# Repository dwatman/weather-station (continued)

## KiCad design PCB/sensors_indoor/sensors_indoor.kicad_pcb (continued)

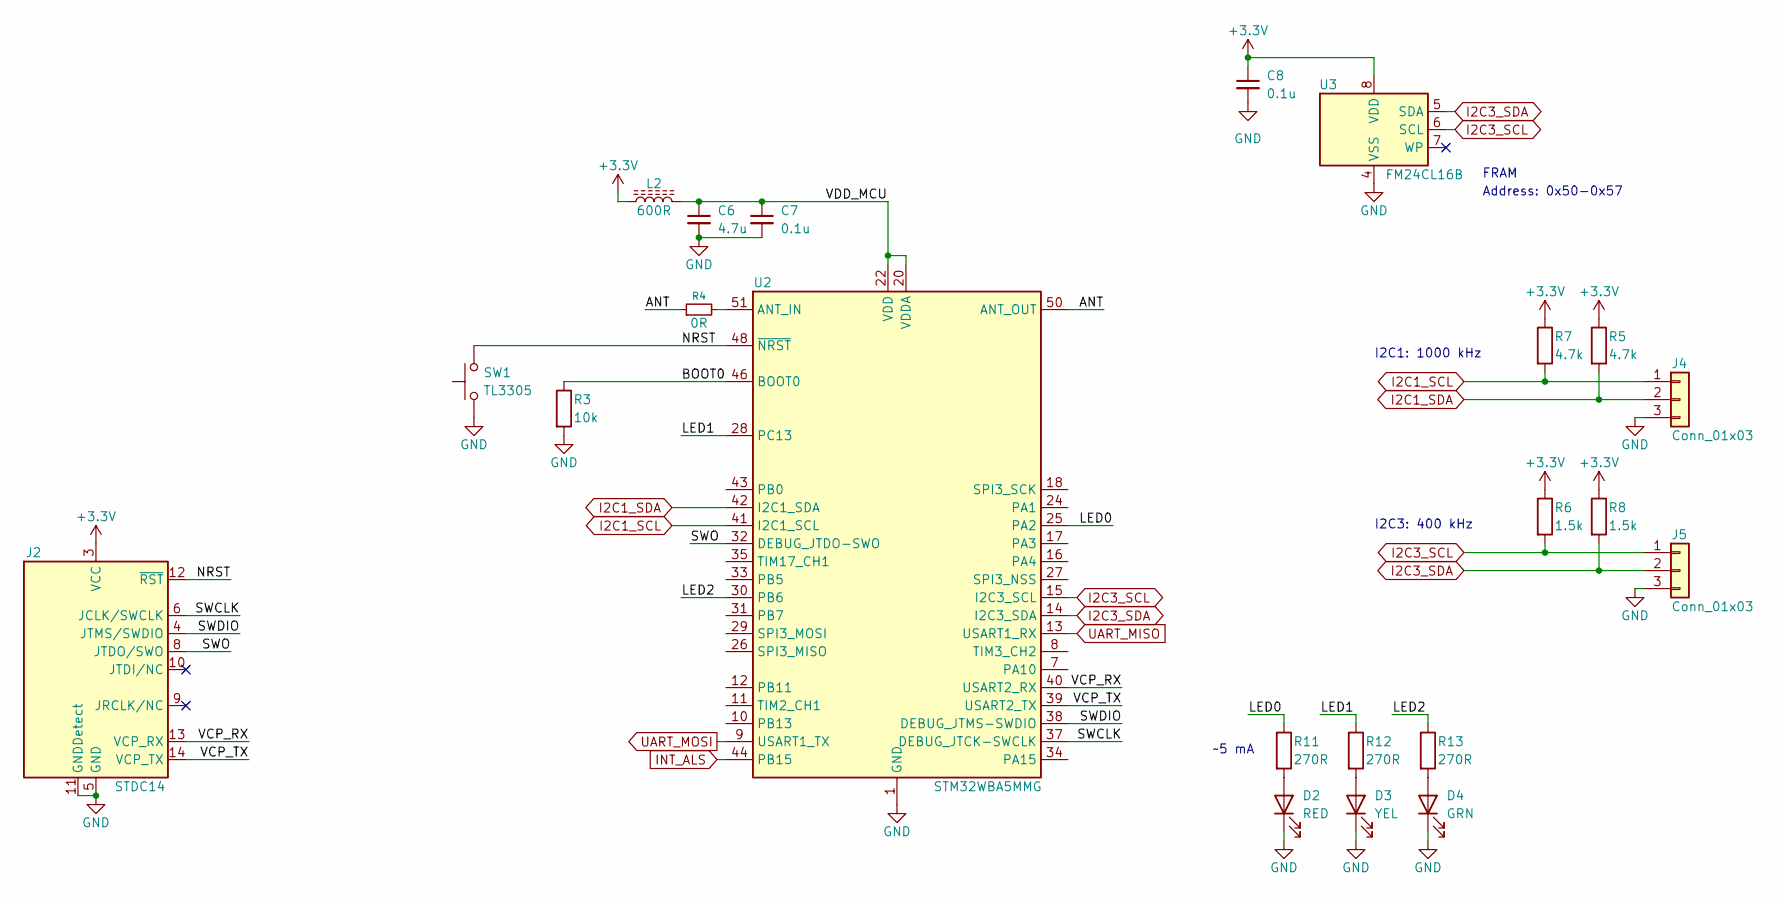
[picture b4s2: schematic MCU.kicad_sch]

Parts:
C6: 4.7u; C_0805_2012Metric
C7, C8: 0.1u; C_0402_1005Metric
D2: RED; LED_0805_2012Metric; MPN LS R976-NR-1-0-20-R18
D3: YEL; LED_0805_2012Metric; MPN LY R976-PS-36-0-20-R18
D4: GRN; LED_0805_2012Metric; MPN LG R971-KN-1-0-20-R18
J2: STDC14; SAMTEC_FTSH-107-01-L-DV-K-A; MPN FTSH-107-01-L-DV-K-A; Mouser PN 200-FTSH10701LDVKA
J4, J5: Conn_01x03; PinHeader_1x03_P2.54mm_Vertical
L2: 600R; L_0805_2012Metric; MPN HZ0805E601R-10; Mouser PN 875-HZ0805E601R-10
R3: 10k; R_0603_1608Metric
R4: 0R; R_0402_1005Metric
R5, R7: 4.7k; R_0603_1608Metric
R6, R8: 1.5k; R_0603_1608Metric
R11, R12, R13: 270R; R_0603_1608Metric
SW1: TL3305; SW_Push_1P1T_NO_E-Switch_TL3305AFxxxQG; MPN TL3305AF260QG; Mouser PN 612-TL3305AF260QG
U2: STM32WBA5MMG; MPN STM32WBA5MMGH6TR; Mouser PN 511-STM32WBA5MMGH6TR
U3: FM24CL16B; SOIC-8_3.9x4.9mm_P1.27mm; MPN FM24CL16B-G; Mouser PN 877-FM24CL16B-G

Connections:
+3.3V: C8.1, J2.3 (VCC), L2.1, R5.1, R6.1, R7.1, R8.1, U3.8 (VDD); also elsewhere on the board
/MCU/ANT: R4.1, U2.50 (ANT_OUT)
/MCU/BOOT0: R3.1, U2.46 (BOOT0)
/MCU/LED0: R11.1, U2.25 (PA2)
/MCU/LED1: R12.1, U2.28 (PC13)
/MCU/LED2: R13.1, U2.30 (PB6)
/MCU/NRST: J2.12 (~RST), SW1.2, U2.48 (~NRST)
/MCU/SWCLK: J2.6 (JCLK/SWCLK), U2.37 (DEBUG_JTCK-SWCLK)
/MCU/SWDIO: J2.4 (JTMS/SWDIO), U2.38 (DEBUG_JTMS-SWDIO)
/MCU/SWO: J2.8 (JTDO/SWO), U2.32 (DEBUG_JTDO-SWO)
/MCU/VCP_RX: J2.13 (VCP_RX), U2.40 (USART2_RX)
/MCU/VCP_TX: J2.14 (VCP_TX), U2.39 (USART2_TX)
/MCU/VDD_MCU: C6.1, C7.1, L2.2, U2.20 (VDDA), U2.22 (VDD)
GND: C6.2, C7.2, C8.2, D2.1 (K), D3.1 (K), D4.1 (K), J2.5 (GND), J2.7 (GND), J2.11 (GNDDetect), J4.3, J5.3, R3.2, SW1.1, U2.1 (GND), U2.6 (GND), U2.19 (GND), U2.21 (GND), U2.23 (GND), U2.36 (GND), U2.45 (GND), U2.47 (GND), U2.49 (GND), U2.52 (GND), U2.53 (GND), U2.54 (GND), U2.55 (GND), U2.57 (GND), U2.58 (GND), U2.60 (GND), U2.61 (GND), U2.62 (GND), U2.63 (GND), U2.64 (GND), U2.65 (GND), U2.66 (GND), U2.67 (GND), U2.68 (GND), U2.69 (GND), U2.70 (GND), U2.71 (GND), U2.72 (GND), U2.73 (GND), U2.74 (GND), U2.75 (GND), U2.76 (GND), U3.4 (VSS); also elsewhere on the board
I2C1_SCL: J4.1, R7.2, U2.41 (I2C1_SCL); also elsewhere on the board
I2C1_SDA: J4.2, R5.2, U2.42 (I2C1_SDA); also elsewhere on the board
I2C3_SCL: J5.1, R6.2, U2.15 (I2C3_SCL), U3.6 (SCL); also elsewhere on the board
I2C3_SDA: J5.2, R8.2, U2.14 (I2C3_SDA), U3.5 (SDA); also elsewhere on the board
INT_ALS: U2.44 (PB15); also elsewhere on the board
unnamed: D2.2 (A), R11.2
unnamed: D3.2 (A), R12.2
unnamed: D4.2 (A), R13.2
unnamed: R4.2, U2.51 (ANT_IN)
UART_MISO: U2.13 (USART1_RX); also elsewhere on the board
UART_MOSI: U2.9 (USART1_TX); also elsewhere on the board

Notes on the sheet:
I2C3: 400 kHz
Address: 0x50-0x57
I2C1: 1000 kHz
FRAM
~5 mA

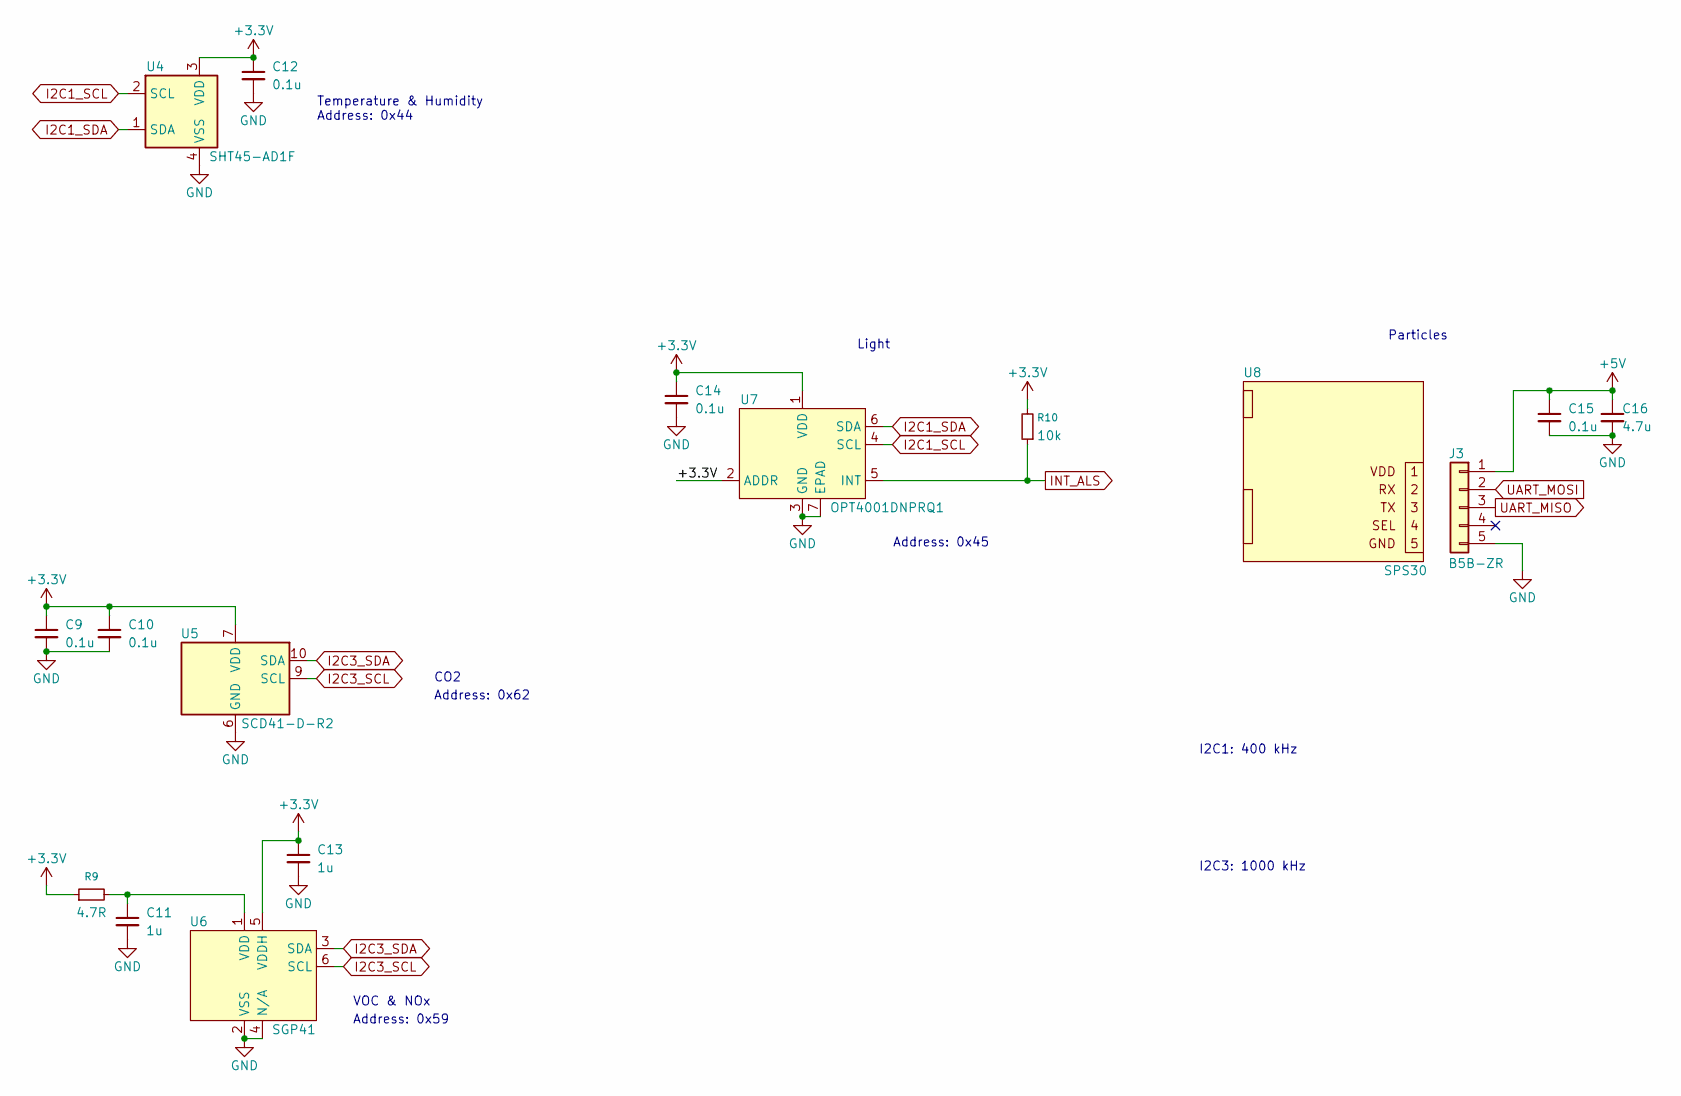
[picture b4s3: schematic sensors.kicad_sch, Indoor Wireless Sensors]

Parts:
C9, C10, C12, C14, C15: 0.1u; C_0402_1005Metric
C11, C13: 1u; C_0402_1005Metric
C16: 4.7u; C_0805_2012Metric
J3: B5B-ZR; JST_ZH_B5B-ZR_1x05_P1.50mm_Vertical; MPN B5B-ZR(LF)(SN); Mouser PN 306-B5BZRLFSNP
R9: 4.7R; R_0603_1608Metric
R10: 10k; R_0603_1608Metric
U4: SHT45-AD1F; Sensirion_DFN-4_1.5x1.5mm_P0.8mm_SHT4x_NoCentralPad; MPN SHT45-AD1F-R2; Mouser PN 403-SHT45-AD1F-R2
U5: SCD41-D-R2; Sensirion_SCD4x-1EP_10.1x10.1mm_P1.25mm_EP4.8x4.8mm; MPN SCD41-D-R2; Mouser PN 403-SCD41-D-R2
U6: SGP41; Sensirion_DFN-6-1EP_2.44x2.44mm_P0.5mm_EP1.25x1.7mm_SGP4x; MPN SGP41-D-R4; Mouser PN 403-SGP41-D-R4
U7: OPT4001DNPRQ1; TI_USON-6-1EP_2x2mm_P0.5mm_EP0.65x1.35mm; MPN OPT4001DNPRQ1; Mouser PN 595-OPT4001DNPRQ1
U8: SPS30; Sensiron_SPS30; MPN SPS30; Mouser PN 403-SPS30

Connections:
+3.3V: C9.1, C10.1, C12.1, C13.1, C14.1, R9.1, R10.2, U4.3 (VDD), U5.7 (VDD), U5.19 (VDD), U6.5 (VDDH), U7.1 (VDD), U7.2 (ADDR); also elsewhere on the board
+5V: C15.1, C16.1, J3.1; also elsewhere on the board
GND: C9.2, C10.2, C11.2, C12.2, C13.2, C14.2, C15.2, C16.2, J3.5, U4.4 (VSS), U5.6 (GND), U5.20 (GND), U5.21 (GND), U6.2 (VSS), U6.4 (N/A), U7.3 (GND), U7.7 (EPAD); also elsewhere on the board
I2C1_SCL: U4.2 (SCL), U7.4 (SCL); also elsewhere on the board
I2C1_SDA: U4.1 (SDA), U7.6 (SDA); also elsewhere on the board
I2C3_SCL: U5.9 (SCL), U6.6 (SCL); also elsewhere on the board
I2C3_SDA: U5.10 (SDA), U6.3 (SDA); also elsewhere on the board
INT_ALS: R10.1, U7.5 (INT); also elsewhere on the board
unnamed: C11.1, R9.2, U6.1 (VDD)
UART_MISO: J3.3; also elsewhere on the board
UART_MOSI: J3.2; also elsewhere on the board

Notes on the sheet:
Address: 0x59
VOC & NOx
Address: 0x44
Particles
CO2
Light
I2C1: 400 kHz
Address: 0x45
I2C3: 1000 kHz
Temperature & Humidity
Address: 0x62

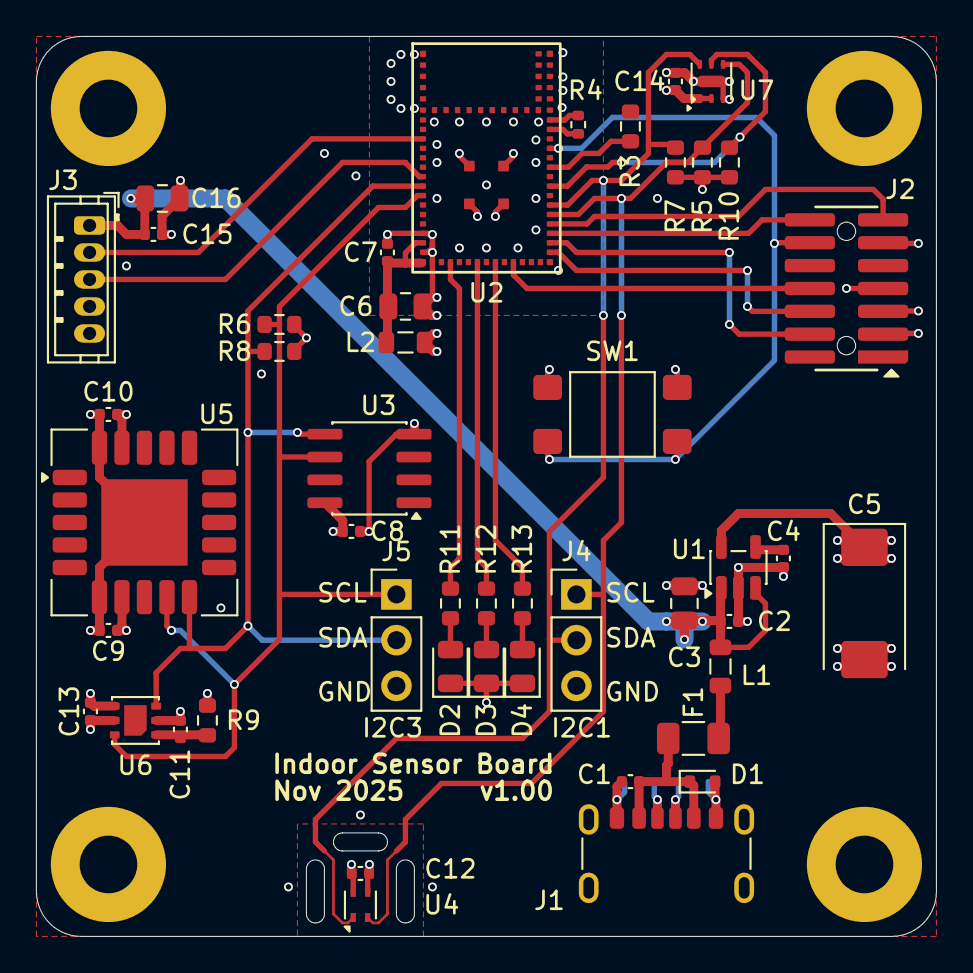
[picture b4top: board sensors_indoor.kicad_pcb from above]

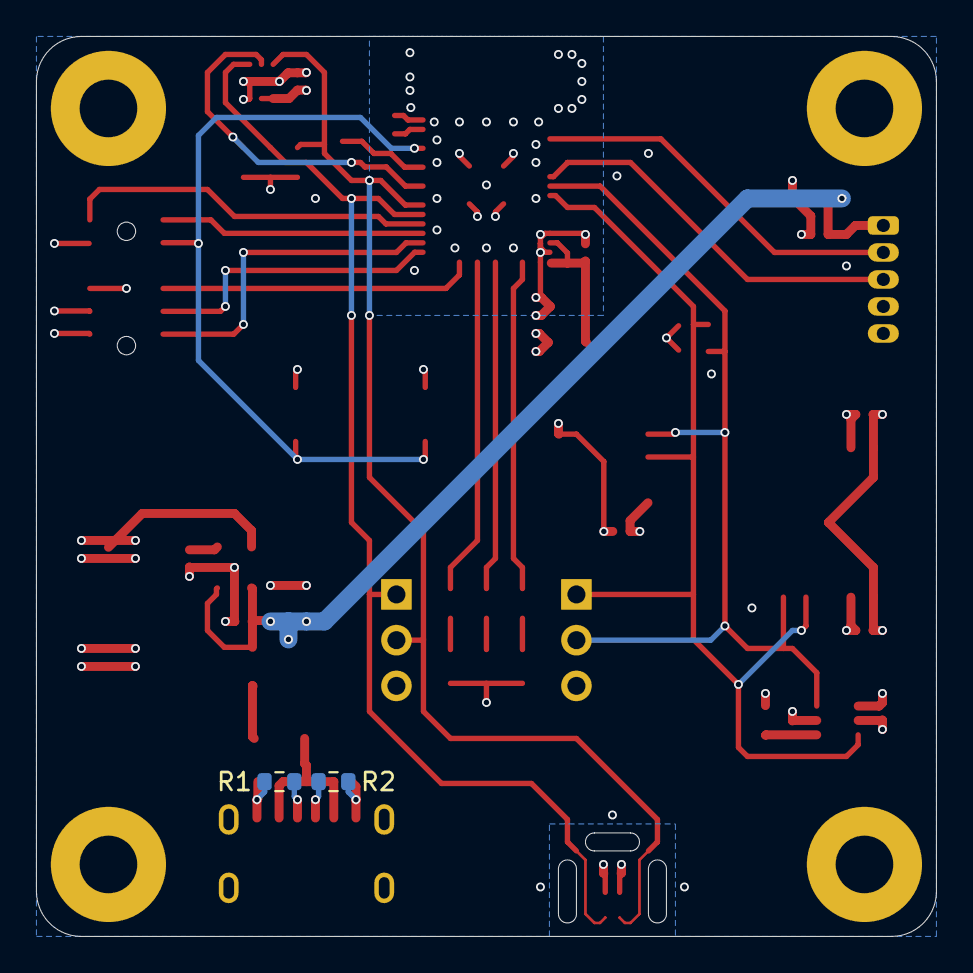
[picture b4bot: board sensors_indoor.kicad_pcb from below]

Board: 4 copper layers, 50.0 x 50.0 mm, 53 parts (2 on the bottom side), 32 nets.

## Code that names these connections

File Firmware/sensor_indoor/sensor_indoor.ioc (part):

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Mcu.Name=STM32WBA5MMGHx
Mcu.Package=LGA76
Mcu.UserName=STM32WBA5MMGHx
PA0.Mode=Full_Duplex_Master
PA0.Signal=SPI3_SCK
PA11.Mode=Asynchronous
PA11.Signal=USART2_RX
PA12.Mode=Asynchronous
PA12.Signal=USART2_TX
PA13\ (JTMS/SWDIO).Mode=Trace_Asynchronous_SW
PA13\ (JTMS/SWDIO).Signal=DEBUG_JTMS-SWDIO
PA14\ (JTCK/SWCLK).Mode=Trace_Asynchronous_SW
PA14\ (JTCK/SWCLK).Signal=DEBUG_JTCK-SWCLK
PA2.GPIOParameters=GPIO_Label
PA2.GPIO_Label=INT_PRES
PA2.Signal=GPIO_Input
PA5.Mode=NSS_Signal_Hard_Output
PA5.Signal=SPI3_NSS
PA6.Mode=I2C
PA6.Signal=I2C3_SCL
PA7.Mode=I2C
PA7.Signal=I2C3_SDA
PA8.Mode=Asynchronous
PA8.Signal=USART1_RX
PA9.Signal=S_TIM3_CH2
PB1.Mode=I2C
PB1.Signal=I2C1_SDA
PB12.Signal=S_TIM2_CH1
PB14.Mode=Asynchronous
PB14.Signal=USART1_TX
PB15.GPIOParameters=GPIO_Label
PB15.GPIO_Label=INT_ALS
PB15.Signal=GPIO_Input
PB2.Mode=I2C
PB2.Signal=I2C1_SCL
PB3\ (JTDO/TRACESWO).Mode=Trace_Asynchronous_SW
PB3\ (JTDO/TRACESWO).Signal=DEBUG_JTDO-SWO
PB4\ (NJTRST).Signal=S_TIM17_CH1
PB8.Mode=Full_Duplex_Master
PB8.Signal=SPI3_MOSI
PB9.Mode=Full_Duplex_Master
PB9.Signal=SPI3_MISO
RCC.HSESYSFreq_VALUE=16000000
RCC.HSE_VALUE=16000000
RCC.SYSCLKFreq_VALUE=16000000
board=custom

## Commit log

2025-09-27 Added gitignore for STM32
2025-09-27 Created project to develop Zigbee application
2025-09-27 Added LED and button connections
2025-09-27 Added simulated temperature measurement. Added persistent storage for Zigbee reconnection
2025-09-27 Changed to reduced function device, endpoint only to reduce code size and complexity
2025-09-27 Created project to test particle sensor
2025-09-28 Added DMA USART transmit function
2025-09-28 Added DMA USART receive functions
2025-09-28 Added burst_end flag to RX
2025-09-29 Added initial files for SPS30 protocol
2025-09-29 Can send reset command, DMA RX works but not looping
2025-09-30 Trying to get circular DMA working, still fails
2025-09-30 Removed attempt to retrigger linear transfer
2025-09-30 Changed DMA mode to use circular linked list
2025-09-30 Circular DMA is working
2025-10-01 Cleaned up some DMA read functions
2025-10-01 Prepare for decoding SPS30 data
2025-10-04 Added functions to receive Sensiron data packets
2025-10-04 Cleaned up unused structures and functions
2025-10-04 Pass usart handle to tx and rx functions for flexibility
2025-10-04 Clear new_data when there is not enough data for the full packet. Moved the buffer for raw bytes to a global to prevent reallocating every time.
2025-10-04 Improved skipping to next marker
2025-10-04 Read particle count data (working!)
2025-10-04 Added functions to calculate 1 minute averages
2025-10-05 Created project for interfacing with SHT40 temperature/humidity sensor
2025-10-05 Added initial I2C functions
2025-10-05 Increased I2C speed to 400kHz, read/write is working
2025-10-05 Restructured to separate the SHT40 from I2C bus so other sensors can share the bus.
2025-10-10 Created KiCad library and initial project with available parts
2025-10-12 Added OPT4001 ambient light sensor, fixed antenna clearance for STM32WBA
2025-10-12 Adjusted gitignore for KiCad
2025-10-12 Arranged sensors on PCB, added MRAM and USB-C socket
2025-10-12 Split schematic into 3 for clarity
2025-10-14 Refined antenna clearance for STM32WBA based on dev board
2025-10-14 Added mounting holes and power supply
2025-10-15 Swapped sides of everything and started routing
2025-10-16 Added IR receiver and LED to library
2025-10-16 Updated PCB with SMD IR tx/rx
2025-10-17 Changed ambient light sensor
2025-10-17 Fixed footprints for IR LED and MCU
2025-10-17 Completed schematic, done most routing
2025-10-18 Added preliminary energy harvesting circuit for solar power
2025-10-19 Improved pressure sensor footprint
2025-10-20 Fixed text width in library
2025-10-20 Placed designators on PCB
2025-10-20 Restructured directories
2025-10-20 Expand README with sensor and module details
    Added specifications for wireless module, sensors, and sensor units.
2025-10-21 Added UV sensor
2025-10-21 Changed switch to SMD type
2025-10-22 Completed routing connections
2025-10-22 Added 18650 battery holder to library and solar PCB
2025-10-29 Renamed PCB test project
2025-10-29 Added SPI version of FRAM to library
2025-11-05 Created indoor sensor PCB
2025-11-05 Changed PTC fuse part
2025-11-06 Added LEDs
2025-11-08 Added u-blox NINA-W13 Wi-Fi module to library
2025-11-08 Started new PCB for wifi module
2025-11-09 Rotated USB-C to exit at bottom, added debug pins for I2C
2025-11-09 Added filtering and connectors to solar PCB with 3D models
2025-11-10 Added light sensor, IR remote sensor, test connectors, and routed PCB for display
2025-11-11 Added passthrough for power and SWD to simplify connections. Added part numbers.
2025-11-24 Added part numbers for cables
2025-11-24 Added skeleton PCB project for outdoor sensor
2025-11-24 Initial IOC for indoor sensor
2025-11-24 Add LVGL demo project
2025-11-24 Add LVGL submodule
2025-11-24 Regenerated project
2025-11-24 Added test items for display
2025-11-24 Fixed LVGL version
2025-11-25 Removed unused peripherals from configuration
2025-11-25 Moved backlight PWM, I2C4, USART1 to CM4. Removed code for touchscreen
2025-11-26 Removed more unused connections and added labels to ALS and WiFi module pins
2025-11-26 Changed HAL to LL where possible
2025-11-26 Added UART4 with FIFO for debug output
2025-11-26 Added initialisation of OPT4001 ambient light sensor
2025-11-26 Added read function for OPT4001
2025-11-26 Added ISR-based printf to serial port for debug
2025-11-26 Updated critical sections in circbuf.c
2025-11-26 Fixed printf
2025-11-26 Added conversion function for OPT4001
2025-11-27 Updated PCB to v1.1
2025-11-27 Removed unused widgets from LVGL config
2025-11-27 Updated the display with more controllable values
2025-11-27 Added EEZ Studio project
2025-11-27 Added hardware semaphore M4->M7 to indicate new data
2025-11-27 Shared memory transfer of lux is working (not optimal yet)
2025-11-27 Add mutex to LVGL so it doesn't get stuck
2025-11-27 Fixed priority and timing
2025-11-28 Added WiFi connectivity image, adjusted included fonts
2025-11-28 Improved transfer of shared data
2025-11-28 Upgraded STM32CubeMX version
2025-11-28 Added shared variable for time, changeable colour of wifi symbol
2025-11-28 Fixed mutex coverage, stops freezes
2025-11-29 Added 96px font and resized text
2025-11-29 Enabled FIFO and DMA receive for USART1
2025-11-29 Set up transmit of AT commands to WiFi module
2025-11-29 Set up DMA receive of serial data from WiFi module
2025-11-30 Added function to clear circular buffer when data is not needed
2025-11-30 Added parsing of control/status messages from WiFi module
2025-12-01 Added pressure, backlight, 4x soil measurements to display
2025-12-04 Added external interrupt from pressure sensor
2025-12-04 Correct reception of data from MQTT
2025-12-05 Added pressure measurement from LPS25HB sensor, integrated
2025-12-05 Round pressure and lux to 1 decimal place
2025-12-10 Regenerated project on laptop
2025-12-10 Added state machine for handling wifi connection
2025-12-10 Debugging state machine - working up to MQTT join
2025-12-10 Updated message parser and state machine - working up to MQTT send
2025-12-10 Fixed problem with detecting OK/ERROR
2025-12-11 Network initialisation state machine fully working
2025-12-11 Sends auto-discovery messages on startup
2025-12-11 MQTT discovery and data sending working
2025-12-11 MQTT data reception working
2025-12-12 Updated display with larger font, 2 more soil sensors, garage door indicator
2025-12-12 Automatic adjustment of backlight brightness
2025-12-12 Added validation of MQTT mesage length before parsing
2025-12-12 Improved the look of graphics
2025-12-12 Added filtering for pressure readings and fast start of backlight brightness adjustment
2025-12-12 Updated IOC for IR code rception with DMA
2025-12-13 Implemented Samsung IR code detection
2025-12-20 Added decoding of IR signal
2025-12-21 Increased backlight PWM resolution
2025-12-22 Increased lux resolution to 3 decimal places
2025-12-22 Updated garage door icon
2025-12-30 [PCB] Changed library over to submodule and updated project
2026-01-09 Added automatic reset of WiFi if no data received for a while, or on IR remote "STOP" command. Fixed release build settings.
2026-01-12 Added more checks to stop it getting stuck on startup or when there are wifi issues
2026-01-17 Added reset if RSSI is low for 1hr
2026-03-31 First attempt to set up IOC
2026-03-31 Added CLAUDE.md
2026-04-01 Generated code with simulated sensors, changed to RFD to fit in RAM.
2026-04-03 Changed power def to mains power
2026-04-05 Fixed hard fault caused by logging function, increased stack size, merged RAM/RAM2. Now connects to coordinator OK
2026-04-06 Removed sound cluster
2026-04-07 Added external converter so Zigbee2MQTT can understand the custom endpoints (NOT WORKING)
2026-04-08 Increased WPAN memory pool and stack size to prevent crash.
2026-04-09 Attempting to fix null values for custom sensors (not working yet)
2026-04-12 Fixed external converter and illuminance conversion function
2026-04-12 Updated project status
